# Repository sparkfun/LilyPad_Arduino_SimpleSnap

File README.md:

LilyPad Arduino SimpleSnap
========================================

[*LilyPad Arduino SimpleSnap (DEV-10941)*](https://www.sparkfun.com/products/10941)

 The SimpleSnap board is similar to the LilyPad Simple board, and has the same functionality except for two major differences: A built-in rechargeable Lithium Polymer battery and female snap connectors. 
 By adding fabric snaps to the board, LilyPad’s made it possible to connect this board to the SimpleSnap Protoboard or simply an arrangement of sew-on fabric snaps so that the board is removable from your project for washing or so that multiple projects can share a board! 

 Repository Contents
-------------------

* **/Hardware** - Eagle design files (.brd, .sch)
* **/Production** - Production panel files (.brd)

Documentation
--------------
* **[SparkFun Fritzing repo](https://github.com/sparkfun/Fritzing_Parts)** - Fritzing diagrams for SparkFun products.
* **[SparkFun 3D Model repo](https://github.com/sparkfun/3D_Models)** - 3D models of SparkFun products. 

License Information
-------------------
This product is _**open source**_! 

The **hardware** is released under [Creative Commons ShareAlike 4.0 International](https://creativecommons.org/licenses/by-sa/4.0/).

Please use, reuse, and modify these files as you see fit. Please maintain attribution to SparkFun Electronics and release anything derivative under the same license.

Distributed as-is; no warranty is given.

- Your friends at SparkFun.

_**Note:** A portion of this sale is given back to Dr. Leah Buechley for continued development and education of e-textiles and also to Arduino LLC to help fund continued development of new tools and new IDE features._

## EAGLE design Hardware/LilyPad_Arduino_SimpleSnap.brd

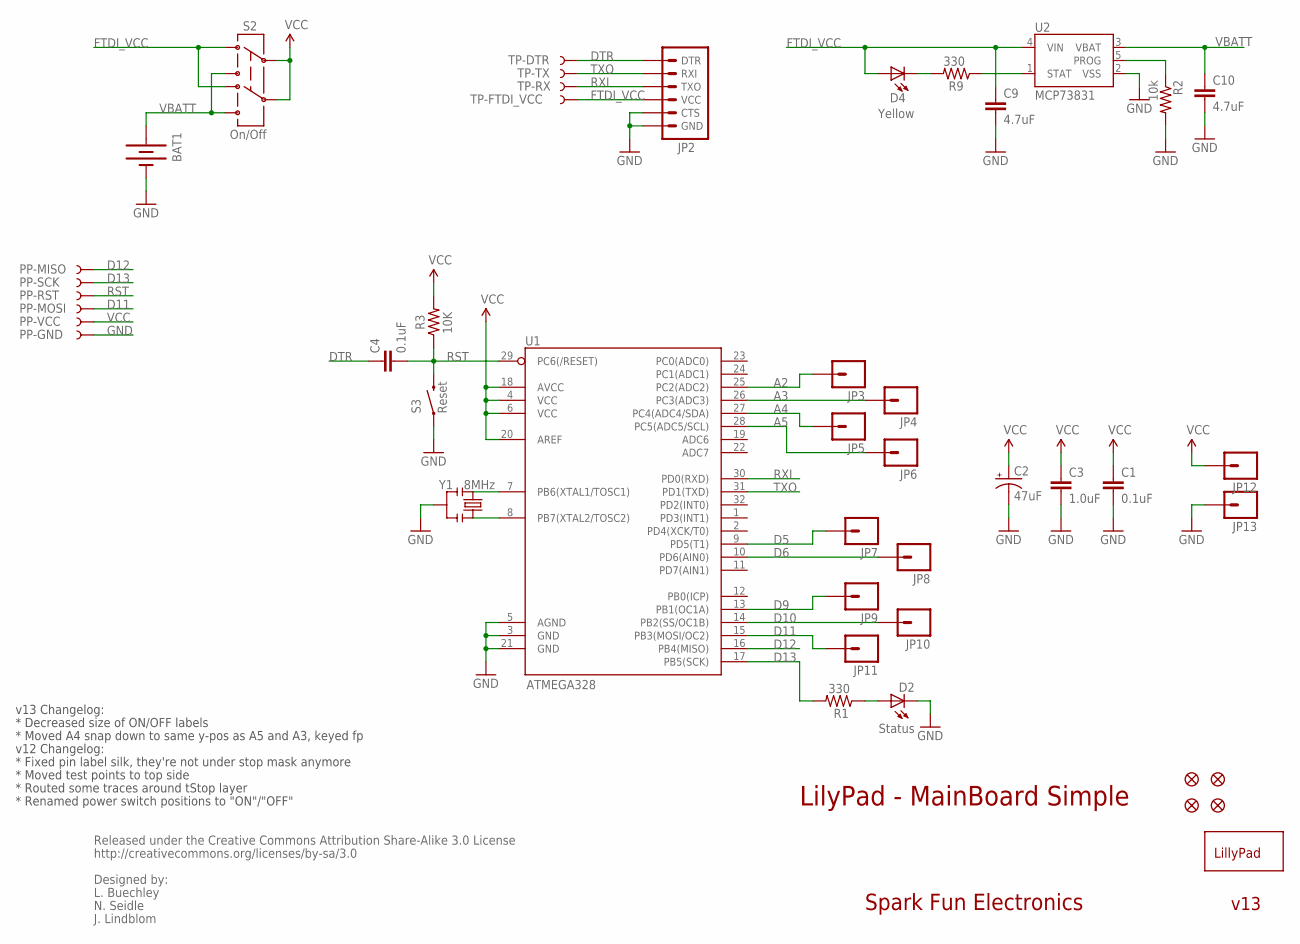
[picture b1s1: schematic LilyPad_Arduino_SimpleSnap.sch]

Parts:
BAT1: BATTERY110-TABS; LIPO-110-TABS
C1, C4: 0.1uF; 0402-CAP
C2: 47uF; EIA3528
C3: 1.0uF; 0402-CAP
C9, C10: 4.7uF; 0402-CAP
D2: Status; LED-0603
D4: Yellow; LED-0603
JP1, JP14, JP15, JP16: FIDUCIALUFIDUCIAL; MICRO-FIDUCIAL
JP2: ARDUINO_SERIAL_PROGRAMSMD; 1X06-SMD
JP3, JP4, JP5, JP6, JP7, JP8, JP9, JP10, JP11, JP12, JP13: M01SNAP-FEMALE_LARGE; SNAP-FEMALE
PP-GND: TEST-POINT3X5; PAD.03X.05
PP-MISO: TEST-POINT3X5; PAD.03X.05
PP-MOSI: TEST-POINT3X5; PAD.03X.05
PP-RST: TEST-POINT3X5; PAD.03X.05
PP-SCK: TEST-POINT3X5; PAD.03X.05
PP-VCC: TEST-POINT3X5; PAD.03X.05
R1, R9: 330; 0402-RES
R2: 10k; 0402-RES
R3: 10K; 0402-RES
S2: On/Off; AYZ0202
S3: Reset; TACTILE_SWITCH_SMD
TP-DTR: TEST-POINT3X5; PAD.03X.05
TP-FTDI_VCC: TEST-POINT3X5; PAD.03X.05
TP-RX: TEST-POINT3X5; PAD.03X.05
TP-TX: TEST-POINT3X5; PAD.03X.05
U1: ATMEGA328; TQFP32-08
U2: MCP73831; SOT23-5
U$2: LOGO-LPLP; LOGO-LILYPAD
Y1: 8MHz; RESONATOR-SMD

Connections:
A2: JP3.1, U1.25 (PC2(ADC2))
A3: JP4.1, U1.26 (PC3(ADC3))
A4: JP5.1, U1.27 (PC4(ADC4/SDA))
A5: JP6.1, U1.28 (PC5(ADC5/SCL))
D5: JP7.1, U1.9 (PD5(T1))
D6: JP8.1, U1.10 (PD6(AIN0))
D9: JP9.1, U1.13 (PB1(OC1A))
D10: JP10.1, U1.14 (PB2(SS/OC1B))
D11: JP11.1, PP-MOSI.P$1, U1.15 (PB3(MOSI/OC2))
D12: PP-MISO.P$1, U1.16 (PB4(MISO))
D13: PP-SCK.P$1, R1.2, U1.17 (PB5(SCK))
DTR: C4.1, JP2.1 (DTR), TP-DTR.P$1
FTDI_VCC: C9.1, D4.A, JP2.4 (VCC), S2.3 (1), S2.6 (4), TP-FTDI_VCC.P$1, U2.4 (VIN)
GND: BAT1.-, C1.2, C2.C (-), C3.2, C9.2, C10.2, D2.C, JP2.5 (CTS), JP2.6 (GND), JP13.1, PP-GND.P$1, R2.2, S3.1, U1.3 (GND), U1.5 (AGND), U1.21 (GND), U2.2 (VSS), Y1.2
unnamed: U1.7 (PB6(XTAL1/TOSC1)), Y1.1
unnamed: D2.A, R1.1
unnamed: U1.8 (PB7(XTAL2/TOSC2)), Y1.3
unnamed: D4.C, R9.2
PROG: R2.1, U2.5 (PROG)
RST: C4.2, PP-RST.P$1, R3.1, S3.3 (2), U1.29 (PC6(/RESET))
RXI: JP2.3 (TXO), TP-RX.P$1, U1.30 (PD0(RXD))
STAT: R9.1, U2.1 (STAT)
TXO: JP2.2 (RXI), TP-TX.P$1, U1.31 (PD1(TXD))
VBATT: BAT1.+, C10.1, S2.1 (3), S2.4 (6), U2.3 (VBAT)
VCC: C1.1, C2.A (+), C3.1, JP12.1, PP-VCC.P$1, R3.2, S2.2, S2.5, U1.4 (VCC), U1.6 (VCC), U1.18 (AVCC), U1.20 (AREF)

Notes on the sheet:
LilyPad - MainBoard Simple
Spark Fun Electronics
Released under the Creative Commons Attribution Share-Alike 3.0 License
http://creativecommons.org/licenses/by-sa/3.0
Designed by:
L. Buechley
N. Seidle
J. Lindblom
v12 Changelog:
* Fixed pin label silk, they're not under stop mask anymore
* Moved test points to top side
* Routed some traces around tStop layer
* Renamed power switch positions to "ON"/"OFF"
v13 Changelog:
* Decreased size of ON/OFF labels
* Moved A4 snap down to same y-pos as A5 and A3, keyed fp
v13

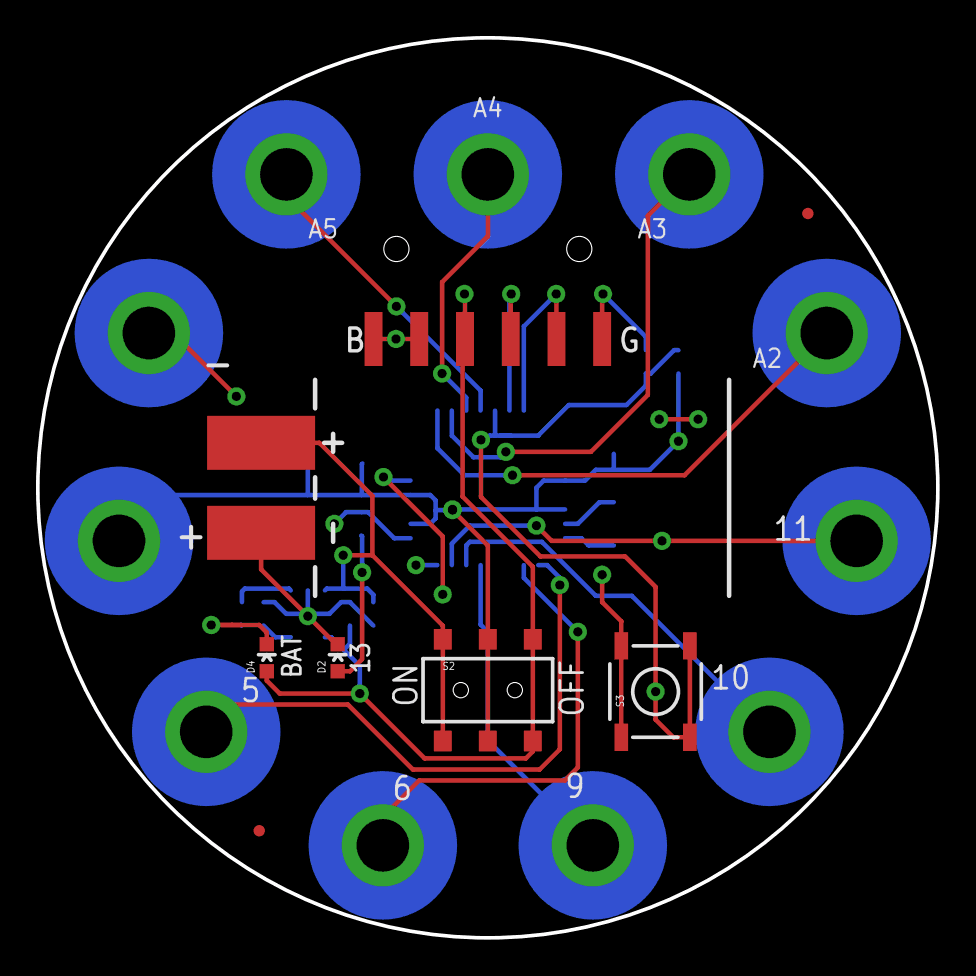
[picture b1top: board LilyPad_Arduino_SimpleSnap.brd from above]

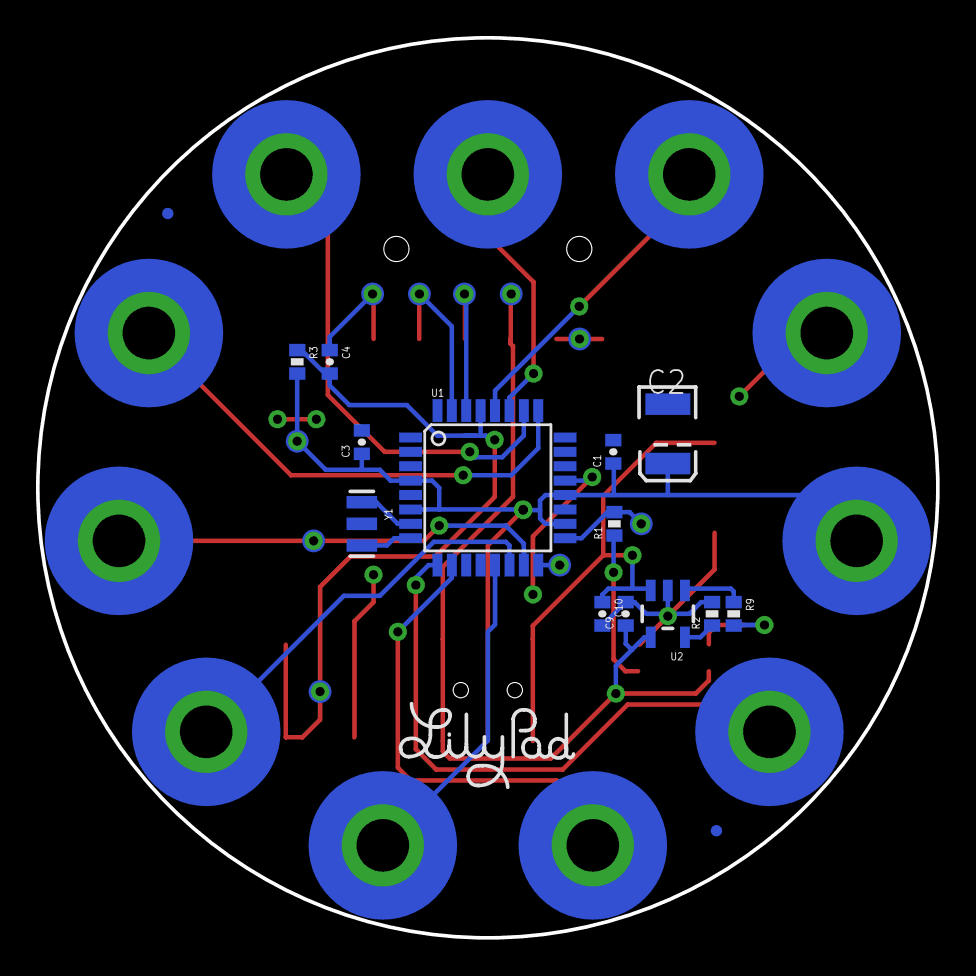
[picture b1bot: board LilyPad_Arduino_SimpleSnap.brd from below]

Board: 2 copper layers, 50.0 x 50.0 mm, 45 parts (37 on the bottom side), 25 nets.

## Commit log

2015-05-06 Adding hardware files, readme
2016-06-23 Fixing resistor value to match actual BOM
2016-06-23 Fixing image URL
